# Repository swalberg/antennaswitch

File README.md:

# Remote antenna switch

This is a remote controller for one of those DIY antenna switch kits. It listens on Wifi for commands and controls the relays. They take a +12V signal to one of 4 relays with a common ground to pick which port is active, and ground the rest:

The firmware for this allows both manual control, and to listen to N1MM+/RUMLogNG broadcasts to pick the band based on configured port/band combinations.

Manual control - go to the web and select the port you want

Auto selection - listens on 12060/UDP for station messages indicating the frequency. You select the antennas that work on each port and it picks the first one. If you go to the web and override it, it'll last until you switch bands.

When the device boots without a config it'll start a new AP for you to configure it.

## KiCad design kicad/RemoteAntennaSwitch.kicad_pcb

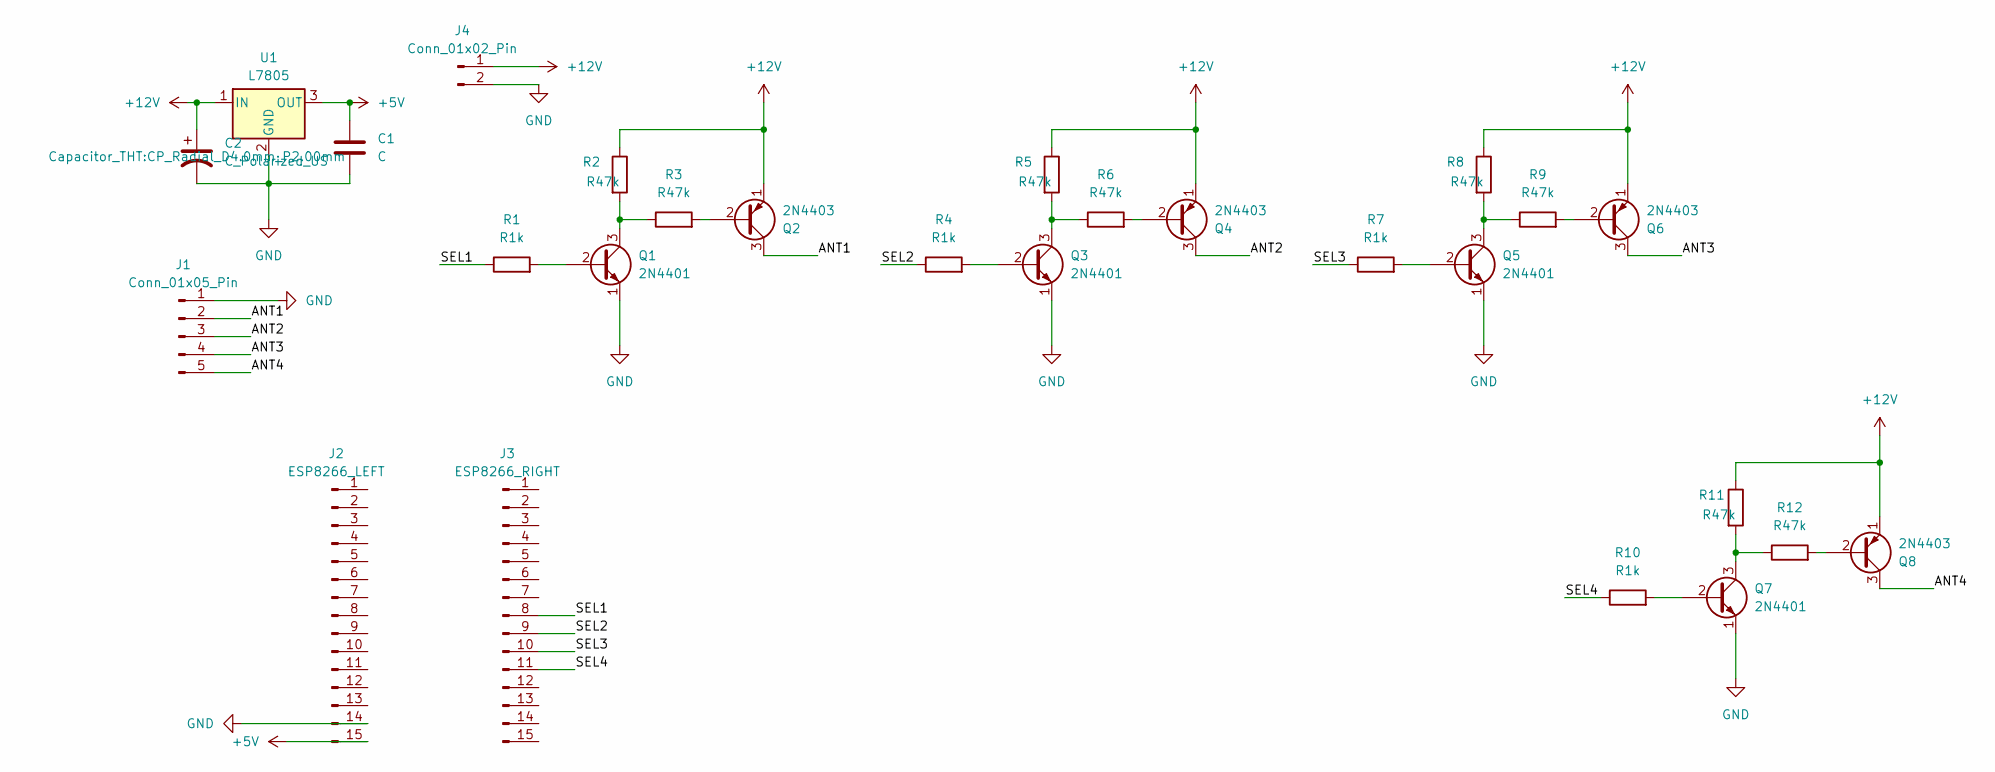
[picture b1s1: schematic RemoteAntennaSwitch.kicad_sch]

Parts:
C1: C; C_Disc_D3.0mm_W1.6mm_P2.50mm
C2: C_Polarized_US; CP_Radial_D4.0mm_P2.00mm
J1: Conn_01x05_Pin; JST_EH_B5B-EH-A_1x05_P2.50mm_Vertical
J2: ESP8266_LEFT; PinHeader_1x15_P1.00mm_Vertical
J3: ESP8266_RIGHT; PinHeader_1x15_P1.00mm_Vertical
J4: Conn_01x02_Pin; PinHeader_1x02_P1.00mm_Vertical
Q1, Q3, Q5, Q7: 2N4401; TO-92_Inline
Q2, Q4, Q6, Q8: 2N4403; TO-92_Inline
R1, R4, R7, R10: R1k; R_Axial_DIN0204_L3.6mm_D1.6mm_P1.90mm_Vertical
R2, R3, R5, R6, R8, R9, R11, R12: R47k; R_Axial_DIN0204_L3.6mm_D1.6mm_P1.90mm_Vertical
U1: L7805; TO-220-3_Vertical

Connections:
+5V: C1.1, J2.15, U1.3 (OUT)
+12V: C2.1, J4.1, Q2.1 (E), Q4.1 (E), Q6.1 (E), Q8.1 (E), R2.1, R5.1, R8.1, R11.1, U1.1 (IN)
/ANT1: J1.2, Q2.3 (C)
/ANT2: J1.3, Q4.3 (C)
/ANT3: J1.4, Q6.3 (C)
/ANT4: J1.5, Q8.3 (C)
/SEL1: J3.8, R1.1
/SEL2: J3.9, R4.1
/SEL3: J3.10, R7.1
/SEL4: J3.11, R10.1
GND: C1.2, C2.2, J1.1, J2.14, J4.2, Q1.1 (E), Q3.1 (E), Q5.1 (E), Q7.1 (E), U1.2 (GND)
unnamed: Q1.2 (B), R1.2
unnamed: Q1.3 (C), R2.2, R3.1
unnamed: Q2.2 (B), R3.2
unnamed: Q3.2 (B), R4.2
unnamed: Q3.3 (C), R5.2, R6.1
unnamed: Q4.2 (B), R6.2
unnamed: Q5.2 (B), R7.2
unnamed: Q5.3 (C), R8.2, R9.1
unnamed: Q6.2 (B), R9.2
unnamed: Q7.2 (B), R10.2
unnamed: Q7.3 (C), R11.2, R12.1
unnamed: Q8.2 (B), R12.2

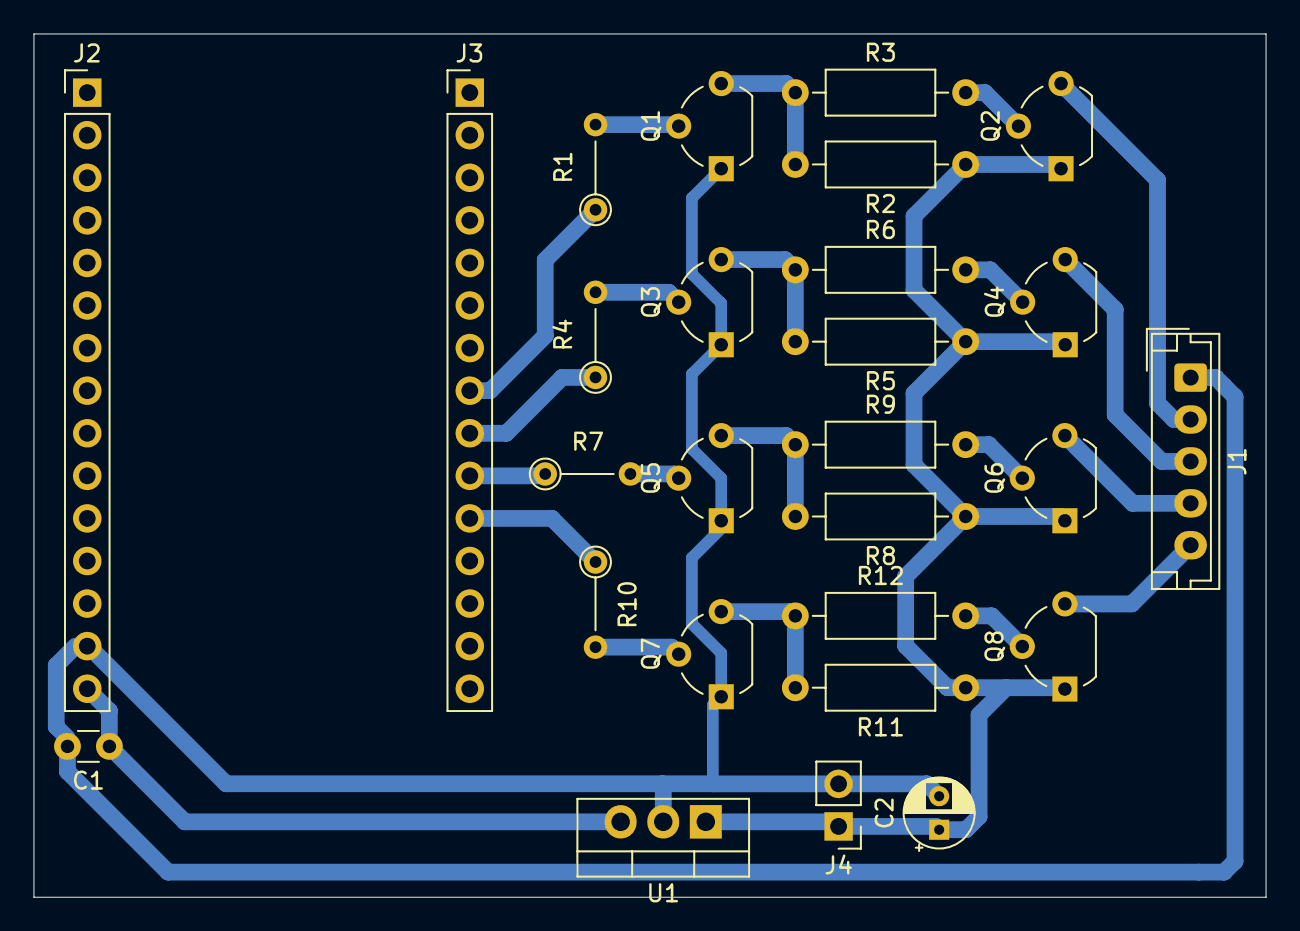
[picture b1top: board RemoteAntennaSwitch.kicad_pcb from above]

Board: 2 copper layers, 73.5 x 51.5 mm, 27 parts (0 on the bottom side), 23 nets.

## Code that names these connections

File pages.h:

const char status_json[] PROGMEM = R"rawliteral(
  {
    "active": %ACTIVE_NUMBER%,
    "antennas": [
      "%ANTENNA0%", "%ANTENNA1%", "%ANTENNA2%", "%ANTENNA3%", "%ANTENNA4%"
    ],
    "manual": %MANUAL%,
    "debug": "%DEBUG%"
  }

)rawliteral";

const char config_wifi[] PROGMEM = R"rawliteral(
<!DOCTYPE HTML>
  <html>Hello from ESP8266 at %IPADDR%!!!
  <p>%FOUND_NETWORKS%</p>
  <form method='post' action='/config_wifi'>
  <label>SSID: </label><input name='ssid' length=32>
  <label>Password: </label><input name='pass' length=64>
  <label>Hostname</label><input name='hostname'><input type='submit'></form>
  </html>
)rawliteral";

const char config_html[] PROGMEM = R"rawliteral(
<!DOCTYPE HTML><html>
<head>
  <title>Antenna switch</title>
  <meta name="viewport" content="width=device-width, initial-scale=1">
  <link rel="icon" href="data:,">
  <style>
    html {font-family: Arial;}
  </style>
</head>
<body>
  <form action="/config" method="POST">
    <table>
    <tr><th>#</th><th>Name</th><th>6M</th><th>10M</th><th>12M</th><th>15M</th><th>17M</th><th>20M</th><th>30M</th><th>40M</th><th>60M</th><th>80M</th><th>160M</th></tr>
    <tr><td><label for="ant0">1</label></td><td><input type="text" name="ant0" value="%ANTENNA0%" placeholder="Antenna1 name">%ANTENNA0BANDS%</tr>
    <tr><td><label for="ant1">2</label></td><td><input type="text" name="ant1" value="%ANTENNA1%" placeholder="Antenna2 name">%ANTENNA1BANDS%</tr>
    <tr><td><label for="ant2">3</label></td><td><input type="text" name="ant2" value="%ANTENNA2%" placeholder="Antenna3 name">%ANTENNA2BANDS%</tr>
    <tr><td><label for="ant3">4</label></td><td><input type="text" name="ant3" value="%ANTENNA3%" placeholder="Antenna4 name">%ANTENNA3BANDS%</tr>
    </table>
    <div><input type="submit"></div>
  </form>
</body>
</html>
)rawliteral";

const char index_html[] PROGMEM = R"rawliteral(
<!DOCTYPE HTML><html>
<head>
  <title>Antenna switch</title>
  <meta name="viewport" content="width=device-width, initial-scale=1">
  <link rel="icon" href="data:,">
  <style>
    html {font-family: Arial; display: inline-block; text-align: center;}
    h2 {font-size: 3.0rem;}
    xxp {font-size: 3.0rem;}
    body {max-width: 600px; margin:0px auto; padding-bottom: 25px;}
    .button { background-color: #195B6A; border: none; color: white; padding: 16px 40px;}
    .button2 {background-color: #77878A;}
    .redbg { background-color: red;}
  </style>
</head>
<body>
  <h1>Remote Antenna Switch - %SWITCH_NAME%</h1>
  <h2>%FLASH_MESSAGE%</h2>
  <table>
  <tr><td>%ANTENNA0%</td><td>%ANTENNA1%</td><td>%ANTENNA2%</td><td>%ANTENNA3%</td><td>GROUND</td></tr>
    <tr><td><p><a href="#"><button class="button" id="0" onClick="change(this)">USE</button></a></p></td>
    <td><p><a href="#"><button class="button" id="1" onClick="change(this)">USE</button></a></p></td>
    <td><p><a href="#"><button class="button" id="2" onClick="change(this)">USE</button></a></p></td>
    <td><p><a href="#"><button class="button" id="3" onClick="change(this)">USE</button></a></p></td>
    <td><p><a href="#"><button class="button" id="99" onClick="change(this)">USE</button></a></p></td></tr>
  
  </table>
  <h2 id="motorStatus"></h2>
  <h3 id="debug"></h3>
  <p>[<a href="/config">Configure ports</a>] [<a href="/config_wifi">Configure wifi</a>]</p>
  <script>
  function change(el) {
    var xhr = new XMLHttpRequest();
    console.log(el);
    console.log(el.id);
    xhr.open("GET", "/change?ant=" + el.id);
    xhr.send();
  }

  setInterval(function () {
    var req = new XMLHttpRequest();
    req.responseType = 'json';
    req.open('GET', "/status.json", true);
    req.onload  = function() {
      var j = req.response;
    
      Array.from(document.getElementsByClassName("button")).forEach(
        function(element, index, array) {
          if (index == j.active) {
            if (j.manual) {
              element.innerHTML = "LOCKED";
            } else {
              element.innerHTML = "ACTIVE";
            }
            element.class = "button button2";
          } else {
            element.innerHTML = "USE";
            element.class = "button";
          }
        }
      );
    };
    req.send();
  }, 2000);

  </script>
</body>
</html>
)rawliteral";


const char debug_html[] PROGMEM = R"rawliteral(
<!DOCTYPE HTML><html>
<head>
  <title>Antenna switch</title>
  <meta name="viewport" content="width=device-width, initial-scale=1">
  <link rel="icon" href="data:,">
  <style>
    html {font-family: Arial; display: inline-block; text-align: center;}
    h2 {font-size: 3.0rem;}
    xxp {font-size: 3.0rem;}
    body {max-width: 600px; margin:0px auto; padding-bottom: 25px;}
    .button { background-color: #195B6A; border: none; color: white; padding: 16px 40px;}
    .button2 {background-color: #77878A;}
    .redbg { background-color: red;}
  </style>
</head>
<body>
  <h1>Remote Antenna Switch - %SWITCH_NAME%</h1>
  <h2>%FLASH_MESSAGE%</h2>
  <table>
  <tr><td>%ANTENNA0%</td><td>%ANTENNA1%</td><td>%ANTENNA2%</td><td>%ANTENNA3%</td><td>GROUND</td></tr>
    <tr><td><p><a href="#"><button class="button" id="on0" onClick="on(0)">ON</button></a></p></td>
    <td><p><a href="#"><button class="button" id="on1" onClick="on(1)">ON</button></a></p></td>
    <td><p><a href="#"><button class="button" id="on2" onClick="on(2)">ON</button></a></p></td>
    <td><p><a href="#"><button class="button" id="on3" onClick="on(3)">ON</button></a></p></td></tr>  

    <tr><td><p><a href="#"><button class="button" id="off0" onClick="off(0)">OFF</button></a></p></td>
    <td><p><a href="#"><button class="button" id="off1" onClick="off(1)">OFF</button></a></p></td>
    <td><p><a href="#"><button class="button" id="off2" onClick="off(2)">OFF</button></a></p></td>
    <td><p><a href="#"><button class="button" id="off3" onClick="off(3)">OFF</button></a></p></td></tr>  
  </table>
  <h3 id="debug">%DEBUG%</h3>
  <script>
  function on(id) {
    var xhr = new XMLHttpRequest();
    xhr.open("GET", "/on?ant=" + id);
    xhr.send();
  }

  function off(id) {
    var xhr = new XMLHttpRequest();
    xhr.open("GET", "/off?ant=" + id);
    xhr.send();
  }

  </script>
</body>
</html>
)rawliteral";

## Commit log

2023-12-17 import
2023-12-17 Cleanup
    I think you need AS5600 v0.4.1 as there are some breaking changes in
    0.5.0
2023-12-22 Almost everything to config struct now
2024-04-24 Move pages to separate file and fixing way we parse input
    Been so long I don't remember :(
2024-12-04 Use the new relay switch
    Got a new antenna switch based on relays, so stop using the stepper
    motor version
2024-12-05 I forgot to set the pins to output
    Also cleaned up antenna switching logic
2024-12-08 Add UDP band decoding
    Both N1MM and RUMLogNG use the same XML for
    q
2025-04-26 Finish moving everything to one loop
    Something's not quite working in config_wifi, it seems to crash.
    Something to do with network scanning, the ESP resets
    Not in a position to console in to get a stack trace now.
    guess I don't need this
2025-04-26 Add kicad files
2025-04-26 Add a README
2025-04-26 image typo
2025-04-27 Add a reset
    If I have a power outage these guys come up before the wifi, so sit on
    the unconfigured network until I walk downstairs to restart them. This
    adds a watchdog timer; if we booted and didn't see our configured
    network in 5 minutes and have not received anything on port 12060 then
    restart
2025-04-28 remove vim swapfile
2025-05-15 Add a locked mode
    If you pick an antenna on the web then that selection is locked until
    the band on the radio changes.
2025-05-18 Adding a debug mode to be able to test the relays
2025-08-24 Enhance README with control features description
    Added details about manual control and auto selection features.
2025-08-24 Clarify manual and auto selection in README
    Updated README to clarify manual and auto selection features.
2026-02-02 Also support PST rotator on N1MM port
2026-02-02 Some debugging of the pins
    Helped when I was trying to figure out why some ports weren't working
2026-02-02 Disable wifi scanning
    I'm not sure what's going on but I get crashes when I try to scan the
    wifi networks and log them.
